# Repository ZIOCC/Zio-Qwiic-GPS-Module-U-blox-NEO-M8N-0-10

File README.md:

# Zio Qwiic GPS Module (U-blox NEO-M8N-0-10)

> This product can be available for purchase [here](https://www.smart-prototyping.com/Zio-Qwiic-GPS-Module-U-blox-NEO-M8N-0-10).

#### Description

GPS is the most interesting part for makers, with GPS, you can know where you are, or state the location of the object that you are tracking. 

This is a high precision GPS module that includes a powerful NEO-M8N-0-10 module from u-blox. 

The NEO-M8N module is based on the u-blox M8 GNSS (GPS, GLONASS, BeiDou, QZSS, SBAS and Galileo-ready1) engine that provides high sensitivity and minimal acquisition times while maintaining low system power.

We used a SC16IS752IPW to convert the module’s data from UART to I2C (Qwiic connectors),  so that you can use [Qwiic cable](https://www.smart-prototyping.com/zio-cables) to quickly connect the GPS module to any other Qwiic devices.
We also breakout the UART port to a 1.27mm terminal connector, just in case you want to use UART port directly.  

We’ve even included a rechargeable backup battery to help keep the latest module configuration and satellite data available for up to two weeks. This battery helps to ‘warm-start’ the module, decreasing the time-to-first-fix dramatically. It also features a survey-in mode allowing the module to become a base station and produce RTCM 3.x correction data (as opposed to the previous version of the module which is not able to produce RTCM data).

We also offer you a tested GPS antenna for the module, you can just plug it into the IPX connector on the board. The antenna is required when you get it running. Note: The antenna needs to face towards the top.

#### Specification

* Voltage: 3.3V
* Horizontal position accuracy: 2.5 m
* Heading accuracy: 0.3 degrees
* Velocity accuracy: 0.05 m/s
* Time-To-First-Fix: 27 - 30s (cold), 1s (hot)
* Interface: I2C and UART

* IC:SC16IS752
* address: 0x4D, 0x4C, 0x49, 0x48 (Default: 0x4D)
* Dimension: 35.5 x 35.8mm
* Weight: 7.8g

#### Links

* [PCB Source file](https://github.com/ZIOCC/Zio-Qwiic-GPS-Module-U-blox-NEO-M8N-0-10/tree/master/EAGLE)
* [PCB schematic](https://github.com/ZIOCC/Zio-Qwiic-GPS-Module-U-blox-NEO-M8N-0-10/blob/master/zio%20qwiic%20gps%20module%20ublox%20schematic%20pdf.pdf)
* [Demo code](https://github.com/toskyRocker/Arduino_Parser_Ublox_Neo_M8N)
* [GPS module NEO-M8N-0-10 datasheet](https://www.u-blox.com/sites/default/files/NEO-M8-FW3_DataSheet_%28UBX-15031086%29.pdf)

###### About Zio
> Zio is a new line of open sourced, compact, and grid layout boards, fully integrated for Arduino and Qwiic ecosystem. Designed ideally for wearables, robotics, small-space limitations or other on the go projects. Check out other awesome Zio products [here](https://www.smart-prototyping.com/Zio).

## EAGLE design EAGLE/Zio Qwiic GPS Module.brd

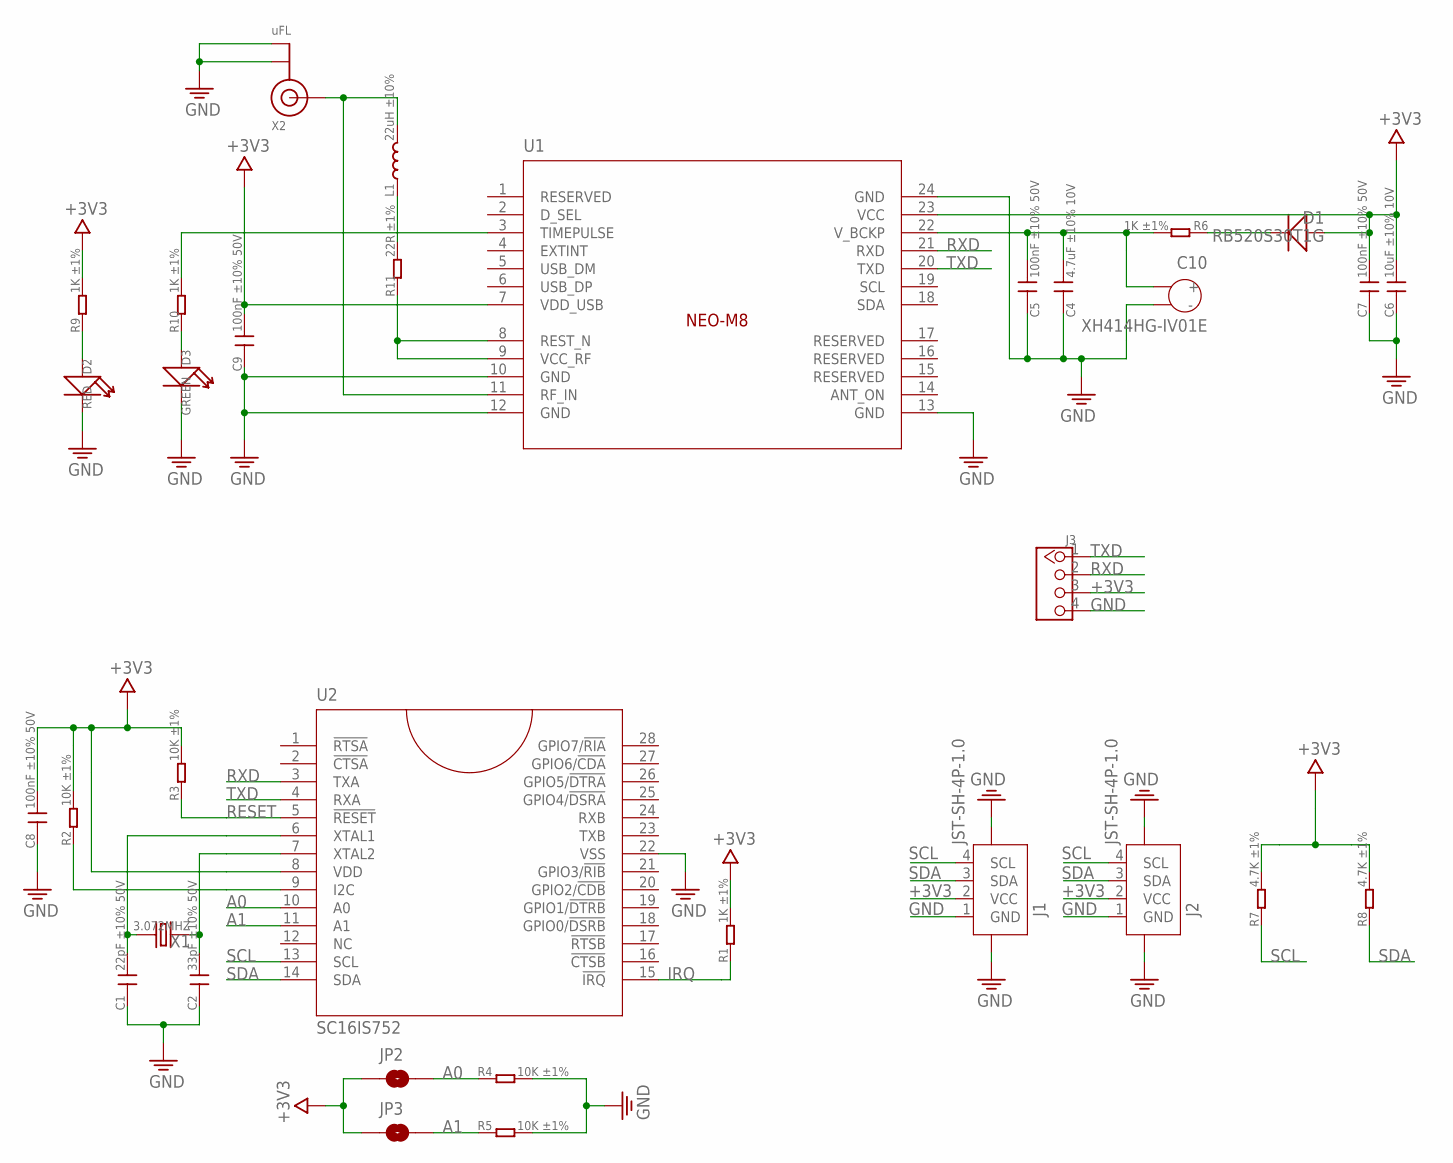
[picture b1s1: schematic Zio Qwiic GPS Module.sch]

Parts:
C1: 22pF ±10% 50V; C0603
C2: 33pF ±10% 50V; C0603
C4: 4.7uF ±10% 10V; C0603
C5, C7, C8, C9: 100nF ±10% 50V; C0603
C6: 10uF ±10% 10V; C0603
C10: XH414HG-IV01E
D1: RB520S30T1G; SOD523
D2: RED; LED-0603
D3: GREEN; LED-0603
J1, J2: JST-SH-4P-1.0; JST-SH-4P
J3: HEADER-4P-1.25-SMD; 4PIN_SMD
JP2, JP3: JUMPER-SMT_2_NC_PASTE_NOCREM; SMT-JUMPER_2_NC_PASTE_SILK_NOCREM
L1: 22uH ±10%; L0603
R1, R6, R9, R10: 1K ±1%; R0603
R2, R3, R4, R5: 10K ±1%; R0603
R7, R8: 4.7K ±1%; R0603
R11: 22R ±1%; R0603
U1: NEO-M8N
U2: SC16IS752; TSSOP28
X1: 3.072MHZ; HC49/S
X2: uFL; U.FL

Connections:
+3V3: C6.2, C7.2, C8.2, C9.2, D1.+, J1.2 (VCC), J2.2 (VCC), J3.3, JP2.1, JP3.1, R1.2, R2.2, R3.2, R7.2, R8.2, R9.2, U1.7 (VDD_USB), U1.23 (VCC), U2.8 (VDD)
A0: JP2.2, R4.1, U2.10 (A0)
A1: JP3.2, R5.1, U2.11 (A1)
GND: C1.1, C2.1, C4.1, C5.1, C6.1, C7.1, C8.1, C9.1, C10.-, D2.-, D3.-, J1.1 (GND), J1.NC1 (5), J1.NC2 (6), J2.1 (GND), J2.NC1 (5), J2.NC2 (6), J3.4, R4.2, R5.2, U1.10 (GND), U1.12 (GND), U1.13 (GND), U1.24 (GND), U2.22 (VSS), X2.1 (GND), X2.2 (GND)
IRQ: R1.1, U2.15 (!IRQ)
unnamed: D1.-, R6.1
unnamed: D2.+, R9.1
unnamed: R10.2, U1.3 (TIMEPULSE)
unnamed: D3.+, R10.1
unnamed: R2.1, U2.9 (I2C)
unnamed: C4.2, C5.2, C10.+, R6.2, U1.22 (V_BCKP)
unnamed: C2.2, U2.7 (XTAL2), X1.1
unnamed: C1.2, U2.6 (XTAL1), X1.2
unnamed: R11.1, U1.8 (REST_N), U1.9 (VCC_RF)
unnamed: L1.1, R11.2
unnamed: L1.2, U1.11 (RF_IN), X2.3 (SIGNAL)
RESET: R3.1, U2.5 (!RESET)
RXD: J3.2, U1.21 (RXD), U2.3 (TXA)
SCL: J1.4 (SCL), J2.4 (SCL), R7.1, U2.13 (SCL)
SDA: J1.3 (SDA), J2.3 (SDA), R8.1, U2.14 (SDA)
TXD: J3.1, U1.20 (TXD), U2.4 (RXA)

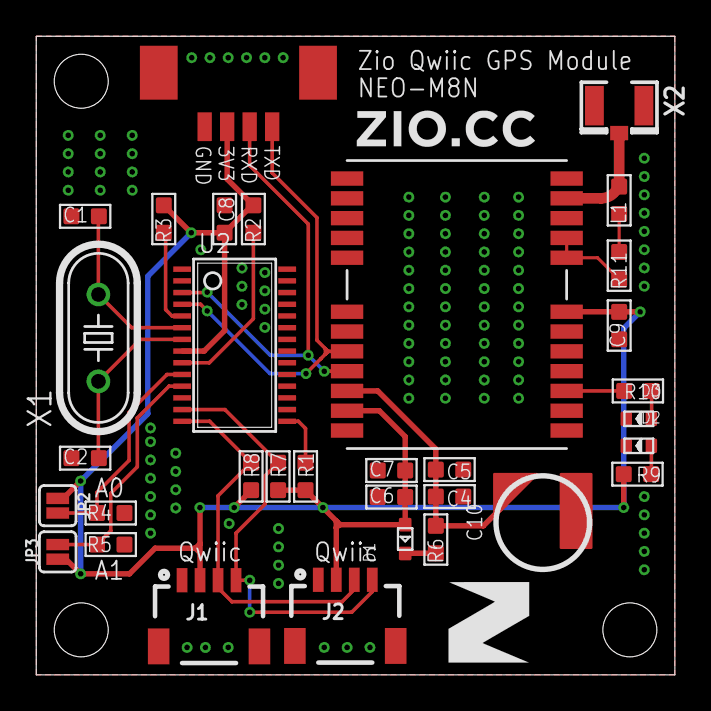
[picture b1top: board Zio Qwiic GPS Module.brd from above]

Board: 2 copper layers, 35.5 x 35.5 mm, 35 parts (0 on the bottom side), 21 nets.

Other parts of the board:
U$7: 7MM
U$8: 2MM

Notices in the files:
parts and their libraries:
microbuilder: This work is placed in the public domain, and may be freely used for commercial and non-commercial work with the following conditions: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
